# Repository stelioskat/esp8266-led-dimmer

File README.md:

# ESP8266 LED Dimmer (MQTT controlled)

1. [Layout](#layout)
  1. [Parts](#parts)
  2. [Schematic](#schematic)
2. [Firmware](#firmware)
  1. [MQTT](#mqtt)

This is a very simple wifi enabled (ESP8266 12e) LED dimmer for single colored LED strips. 

Its purpose was originally to be controlled by Node-RED (http://nodered.org) and node-red-contrib-homekit (https://flows.nodered.org/node/node-red-contrib-homekit) using MQTT events. Thus, one could control this with Apple Homekit.

Of course by using MQTT you can control it with whatever you like and not necessarily with Apple Homekit.

## Layout

The layout is made with KiCad but I have also included an screenshot of the schematic, in case you want to make your own PCB with another software. You could simply produce this PCB for example by uploading the `ESPDimmer.kicad_pcb` file directly in [AISLER](https://go.aisler.net) .

### Parts
<table>
<tr>
  <th>
    Nr.
  </th>
  <th>
    Part
  </th>
  <th>
    Package
  </th>
  <th>
    Qty.
   </th>
</tr>
<tr>
  <td>1</td>
  <td>Capacitor 100nF</td>
  <td>0402</td>
  <td>2</td>
</tr>
<tr>
  <td>2</td>
  <td>Capacitor 1uF</td>
  <td>Package 0402</td>
  <td>1</td>
</tr>
<tr>
  <td>3</td>
  <td>Resistor 10k</td>
  <td>Package 0805</td>
  <td>1</td>
</tr>
<tr>
  <td>4</td>
  <td>Voltage regulator TLV1117</td>
  <td>SOT-223</td>
  <td>1</td>
</tr>
<tr>
  <td>5</td>
  <td>AK300-2 Terminal for LED strip</td>
  <td>-</td>
  <td>1</td>
</tr>
<tr>
  <td>6</td>
  <td>ESP8266-12E</td>
  <td></td>
  <td>1</td>
</tr>
<tr>
  <td>7</td>
  <td>Standard barrel jack for power supply</td>
  <td></td>
  <td>1</td>
</tr>
 <tr>
  <td>8</td>
  <td>30V Single N-Channel Power MOSFET</td>
  <td>TO-220</td>
  <td>1</td>
</tr>
</table>

### Schematic

## Firmware

The firmware can be compiled in Arduino IDE using the available ESP8266 package. In order to flash the firmware you will need a USB-to-Serial adapter such as the FTDI232 that I am using (https://github.com/jandelgado/arduino/wiki/FTDI232-USB-to-Serial-converter). Keep in mind that you will have to update the Wifi credentials and also the MQTT broker hostname and port to fit your own.

Of course, you could write your own firmware or you use another one since this is basically a breakout board.

### MQTT

The default firmware subscribes to the topic "/light/1" and expects the following JSON messages to control the LED strip and its brightness.

- Turn on command:
```
{"On":1}
```
- Turn off command:
```
{"On":0}
```
- Set brightness level:
```
{"Brightness":<A VALUE BETWEEN 0 AND 100>}
```

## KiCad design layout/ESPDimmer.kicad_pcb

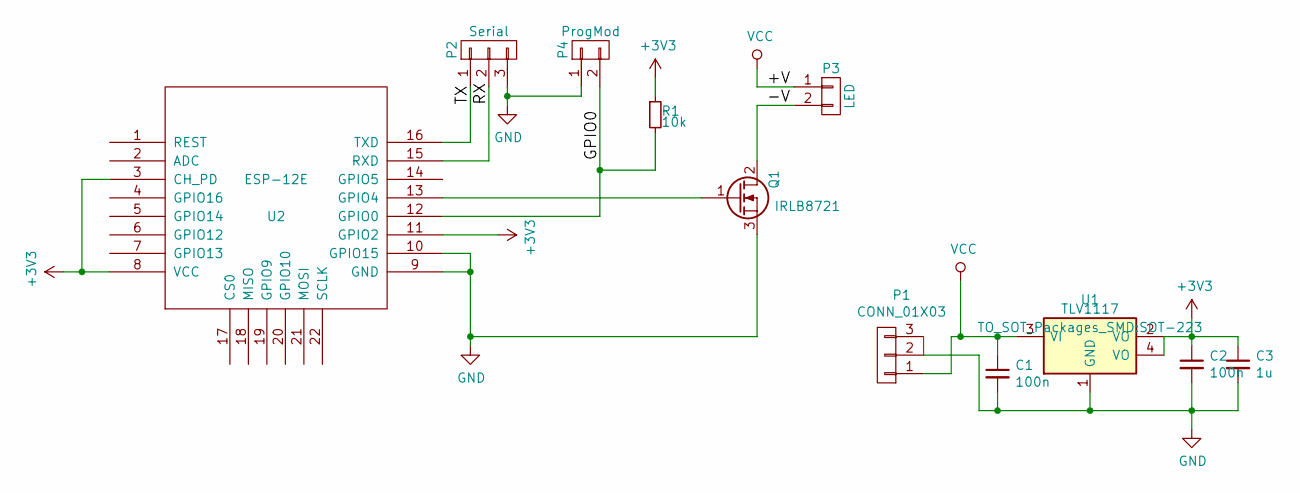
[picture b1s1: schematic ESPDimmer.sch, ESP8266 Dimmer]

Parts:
C1, C2: 100n; C_0402
C3: 1u; C_0402
P1: CONN_01X03; BARREL_JACK
P2: Serial; Socket_Strip_Straight_1x03
P3: LED; AK300-2
P4: ProgMod; Socket_Strip_Straight_1x02
Q1: IRLB8721; TO-220_Neutral123_Vertical
R1: 10k; R_0805
U1: TLV1117; SOT-223
U2: ESP-12E

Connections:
+3V3: C2.1, C3.1, R1.1, U1.2 (VO), U1.4 (VO), U2.3 (CH_PD), U2.8 (VCC), U2.11 (GPIO2)
/-V: P3.2, Q1.2 (D)
/GPIO0: P4.2, R1.2, U2.12 (GPIO0)
/RX: P2.2, U2.15 (RXD)
/TX: P2.1, U2.16 (TXD)
GND: C1.2, C2.2, C3.2, P1.2, P1.3, P2.3, P4.1, Q1.3 (S), U1.1 (GND), U2.9 (GND), U2.10 (GPIO15)
unnamed: Q1.1 (G), U2.13 (GPIO4)
VCC: C1.1, P1.1, P3.1, U1.3 (VI)

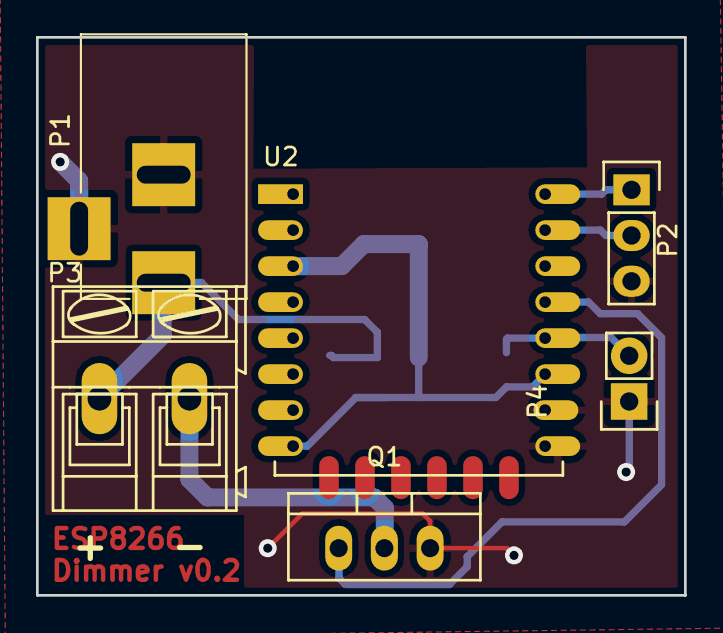
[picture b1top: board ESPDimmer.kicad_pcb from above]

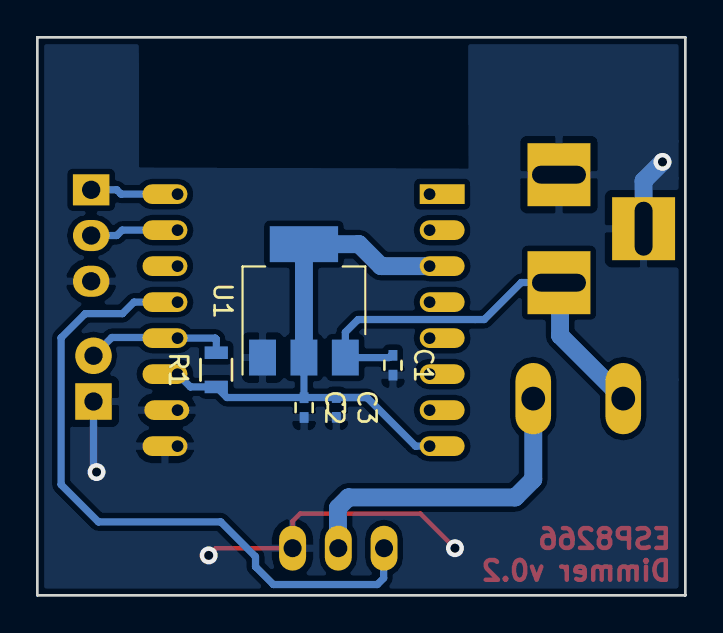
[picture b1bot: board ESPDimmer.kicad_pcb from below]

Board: 2 copper layers, 36.0 x 31.0 mm, 11 parts (5 on the bottom side), 8 nets.

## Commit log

2016-12-30 Added version 0.1 of the PCB
    The dimmer also features an optional DS18B20 thermometer, because why not? :D
2016-12-30 Updated part names and corrected the power supply traces that were shorted!
2016-12-30 Added some vias for better grounding
2016-12-30 Updated capacitors and other small changes
2016-12-31 Initial firmware version. Supports on/off and custom brightness using MQTT messages
2016-12-31 Generic ssid and password
2016-12-31 First version of firmware
2016-12-31 Added pull-up resistor needed for the OneWire communication with the DS18B20 thermometer.
2016-12-31 Added some pictures
2016-12-31 Create README.md with schematic screenshot
2016-12-31 Create LICENSE
2016-12-31 Update firmware to check if the led strip is already on/off and correspondingly apply new changes or not
2017-01-01 Added support for the Dallas DS18B20 thermometer which is on board.
    The firmware broadcasts the current temperature every 5 seconds with an MQTT message with topic “/temp/1”
2017-01-01 Increased temperature reading update interval to 5 minutes and added more comments.
2017-01-01 Added bottom and top layer images
2020-11-22 Some cleanup and small fixes
2020-11-22 Removed thermometer because its readings were incorrect due to the thermal release of the voltage regulator
2020-11-22 Removed thermometer support because it works unreliably.
2020-11-22 The dimmer now publishes a MQTT message with its current status, once it connects to the MQTT broker
